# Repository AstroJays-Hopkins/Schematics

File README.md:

# Schematics

Permanent repository for schematics for all custom electrical hardware that is
created on this team. All custom electric devices, even non PCBs, should have 
a schematic here so we don't lose work.

## Development

Do note that KiCAD isn't fully merge compatible, so check with other people who
might be working on the schematic you modify before changing it. Changes to the
same file at the same time do no usually merge without manual intervention, so
one changeset will usually overwrite the other, causing loss of work.

### Prereqs

- KiCAD (install from [here](https://kicad-pcb.org/download/))
- FreeCAD (Optional, only needed if you need to make footprints or fix 3d models
  for mechanical)
- Understanding of good schematic drawing practices (see our resources section
  to learn more)

### Setup

1. Install KiCAD with 3D models if you have the disk space to spare. This will
   allow you to check you work with a board render
2. Open the `.pro` file with the same name as the project folder. All of the
   other `.pro` files are for the subsheets and should not be opened
   individually.

## Listing

- Actuator PCB - schematics for the circuits that control the higher voltage
  devices such as valves and solenoids
- Ignition-System - Provisional ignition control box ("football") schematics.
  Inaccurate due to missing wires in football and broken connections.
- Lib - Unified repository for all footprints, symbols and 3D models of the
  parts.
- Processor PCB - Schematics for the circuits that handle power distribution and
  inter-MCU communication.
- Prop-Avionics - Schematics for the (legacy) propulsion avionics system and
  DAQ plane
- Recovery PCB - Schematics for the circuits that control recovery ops such as
  altimeter and parachute deployment.
- Sensors PCB - Schematics for the circuits that handle analog to digital
  conversion and the filtering that goes with that.
- SolenoidRelay1 - Schematic for the solenoid control relay for connection to
  the raspberry pi.
- Transole - Prototype transistor based solenoid switching using GPIO level
  outputs and a heckin' large transistor (n-channel MOSFET). This is a *untested
  prototype* and should not be used in production until more research has been
  completed. Credit Sasha and Lin for research and design

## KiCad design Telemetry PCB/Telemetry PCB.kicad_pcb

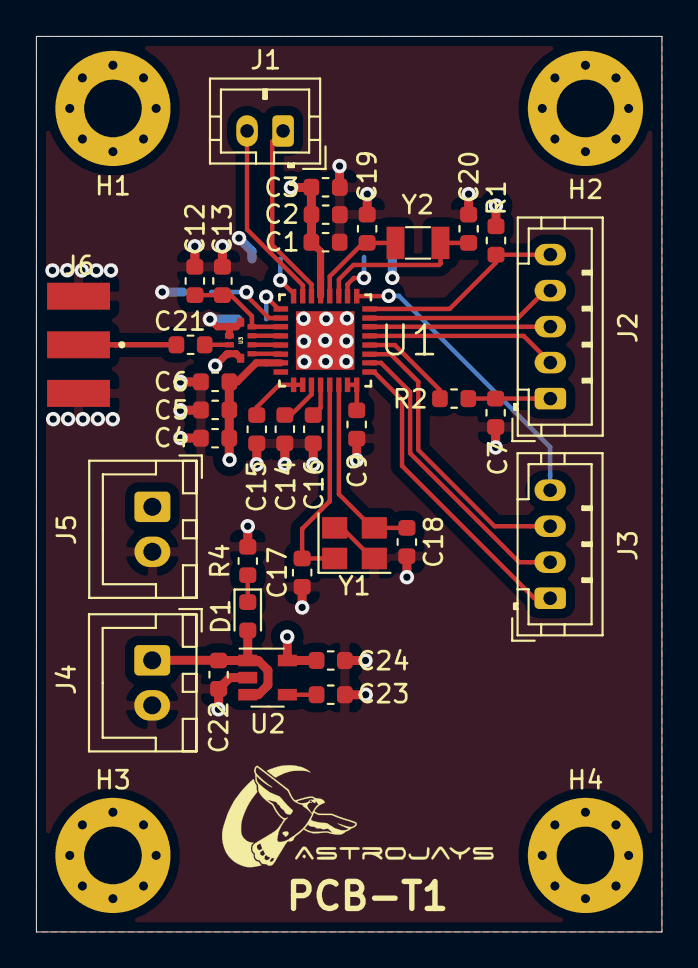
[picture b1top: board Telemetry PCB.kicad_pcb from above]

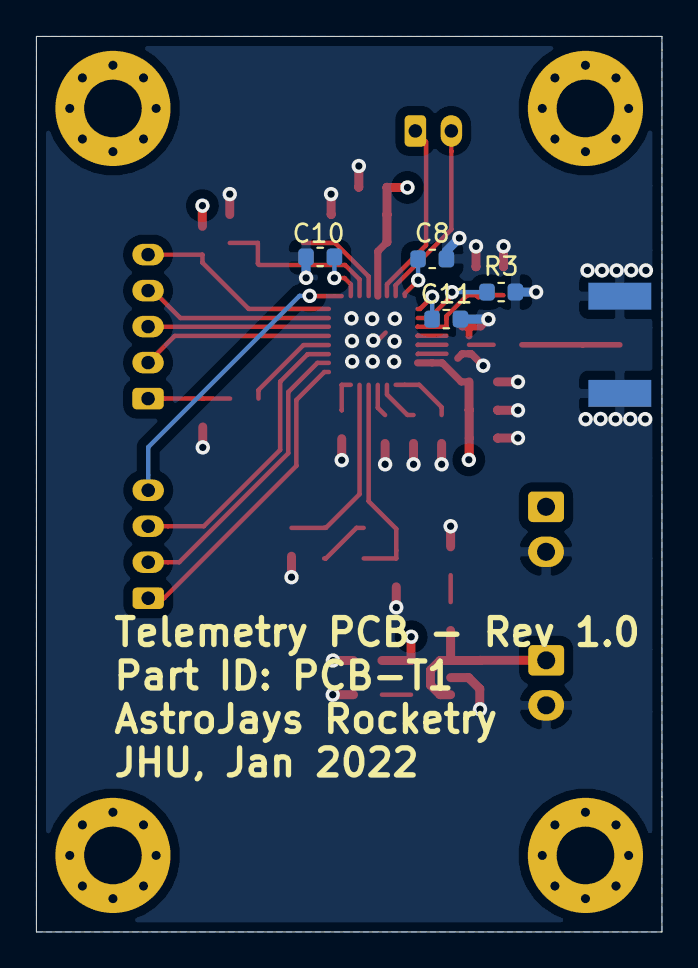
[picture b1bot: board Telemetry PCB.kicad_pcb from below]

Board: 4 copper layers, 34.8 x 49.8 mm, 44 parts (4 on the bottom side), 35 nets.

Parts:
C1, C4: 10u; C_0603_1608Metric
C2, C5, C8, C9, C10, C11, C12, C14, C15: 220n; C_0603_1608Metric
C3, C6: 100p; C_0603_1608Metric
C7: 1.5n; C_0603_1608Metric
C13, C17, C18: 18p; C_0603_1608Metric
C16: 150n; C_0603_1608Metric
C19, C20: 5.6p; C_0603_1608Metric
C21: 56p; C_0603_1608Metric
C22, C24: 2.2u; C_0603_1608Metric
C23: 10n; C_0603_1608Metric
D1: LED; LED_0603_1608Metric
H1, H2, H3, H4: MountingHole; MountingHole_3.2mm_M3_Pad_Via
J1: Conn_01x02_Male; JST_PH_B2B-PH-K_1x02_P2.00mm_Vertical
J2: Conn_01x05_Male; JST_PH_B5B-PH-K_1x05_P2.00mm_Vertical
J3: Conn_01x04_Male; JST_PH_B4B-PH-K_1x04_P2.00mm_Vertical
J4, J5: Conn_01x02_Male; JST_XH_B2B-XH-A_1x02_P2.50mm_Vertical
J6: CON-SMA-EDGE-S; RFSOLUTIONS_CON-SMA-EDGE-S
R1: 100k; R_0603_1608Metric
R2: 1.1k; R_0603_1608Metric
R3: 36k; R_0603_1608Metric
R4: 330; R_0603_1608Metric
U1: ADF7023-JBCPZ; QFN50P500X500X80-33N
U2: LP2985-3.3; SOT-23-5
U3: 0900PC15F0030
Y1: 26M; Crystal_SMD_3225-4Pin_3.2x2.5mm
Y2: 32.768k; Crystal_SMD_3215-2Pin_3.2x1.5mm

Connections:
+3V3: C1.1, C2.1, C3.1, C4.1, C5.1, C6.1, C24.1, J5.1, R1.2, U1.7, U1.29, U2.5
+5V: C22.1, D1.2, J4.1, U2.1, U2.3
/CREGRF2: C12.1, C13.1, U1.3, U3.9
/GP0: J3.1, U1.17
/GP1: J3.2, U1.18
/GP2: J3.3, U1.19
/GP4: J3.4, U1.25
/IRQ: R2.1, U1.20
/LNA_EN: J1.2, U1.31
/MISO: J2.2, U1.21
/MOSI: J2.4, U1.23
/OSC1: C20.1, U1.27, Y2.2
/OSC2: C19.1, U1.28, Y2.1
/PA_EN: J1.1, U1.30
/RFIO_1N: U1.5, U3.7
/RFIO_1P: U1.4, U3.8
/RFO2: U1.6, U3.6
/SCLK: J2.3, U1.22
/~CS: J2.5, R1.1, U1.24
GND: C1.2, C2.2, C3.2, C4.2, C5.2, C6.2, C7.1, C8.2, C9.2, C10.2, C11.2, C12.2, C13.2, C14.2, C15.2, C16.2, C17.2, C18.2, C19.2, C20.2, C22.2, C23.2, C24.2, J4.2, J5.2, J6.G1, J6.G2, J6.G3, J6.G4, R3.2, R4.2, U1.33, U2.2, U3.1, U3.2, U3.4, U3.5, U3.10, Y1.2, Y1.4
unnamed: C7.2, J2.1, R2.2
unnamed: C8.1, U1.32
unnamed: C9.1, U1.15, U1.16
unnamed: C10.1, U1.26
unnamed: C11.1, U1.1
unnamed: C14.1, U1.11
unnamed: C15.1, U1.9, U1.10
unnamed: C16.1, U1.12
unnamed: C17.1, U1.13, Y1.1
unnamed: C18.1, U1.14, Y1.3
unnamed: C21.1, U3.3
unnamed: C21.2, J6.1
unnamed: C23.1, U2.4
unnamed: D1.1, R4.1
unnamed: R3.1, U1.2

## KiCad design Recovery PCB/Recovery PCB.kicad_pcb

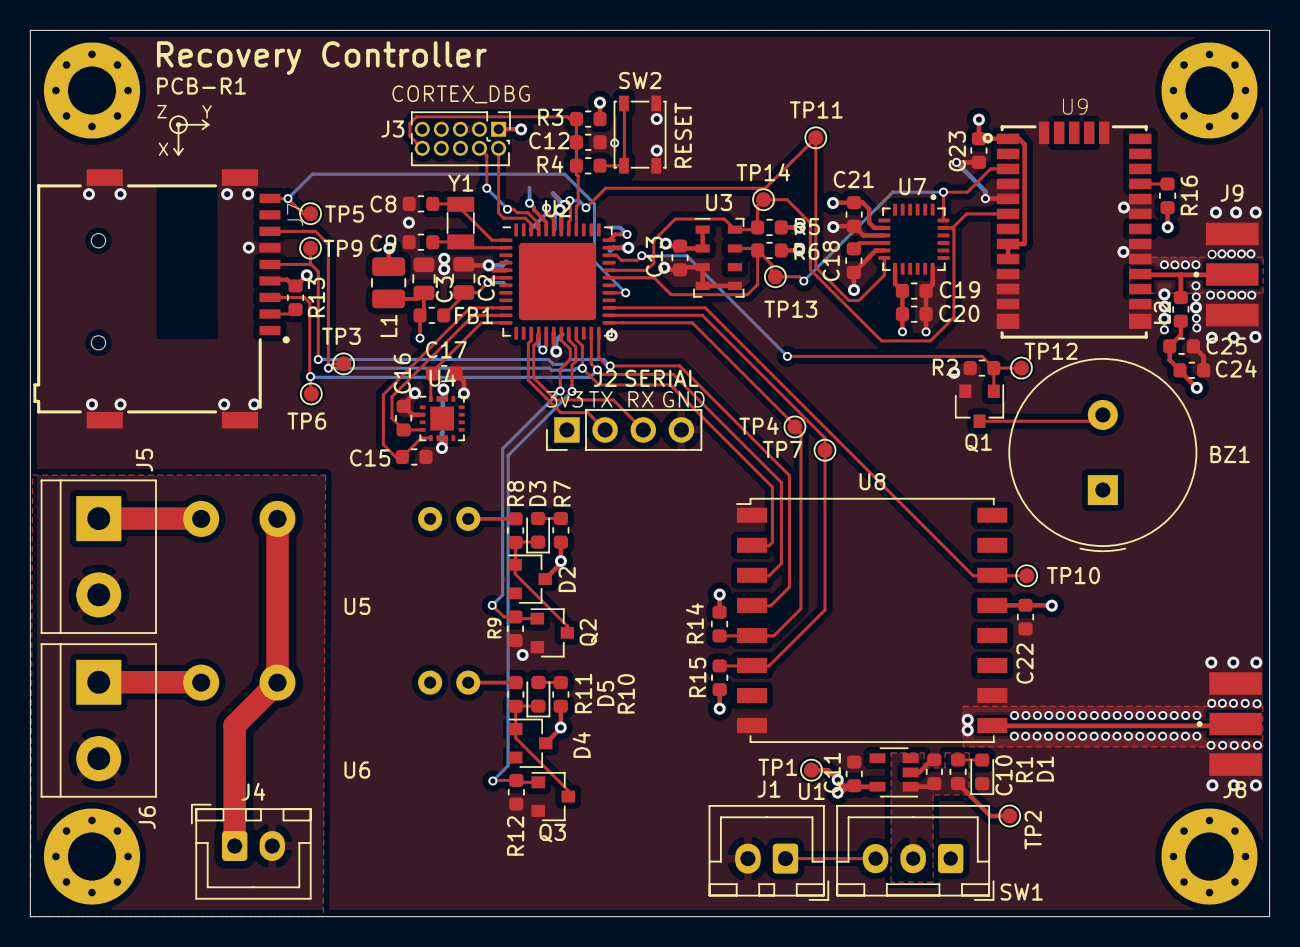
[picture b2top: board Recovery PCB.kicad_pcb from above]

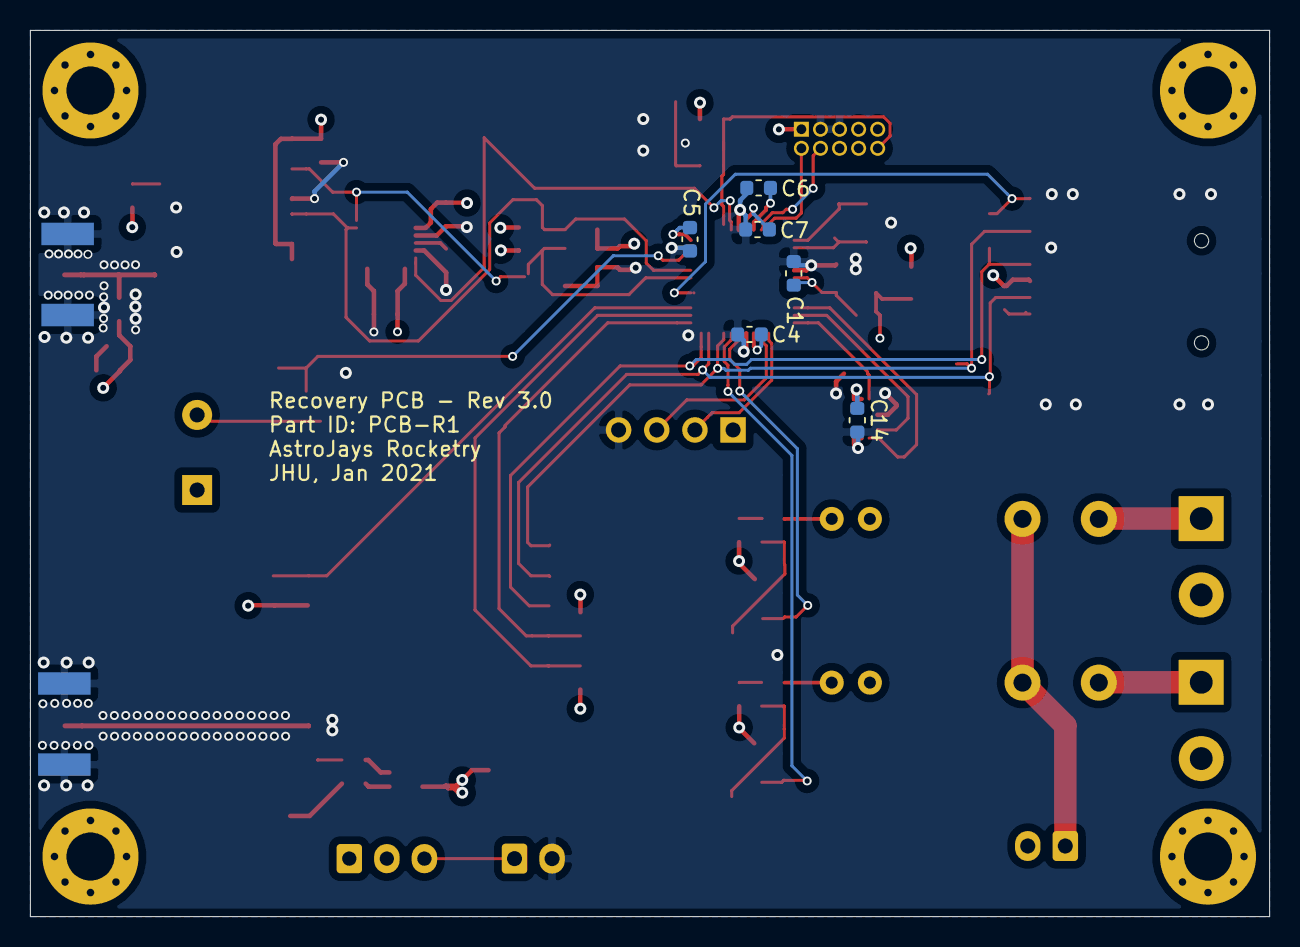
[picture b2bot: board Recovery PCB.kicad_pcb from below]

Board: 4 copper layers, 82.5 x 59.0 mm, 91 parts (6 on the bottom side), 48 nets.

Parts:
BZ1: Buzzer; Buzzer_TDK_PS1240P02BT_D12.2mm_H6.5mm
C1, C4, C5, C6, C12, C13, C14, C20, C22: 0.1u; C_0603_1608Metric
C2, C3: 10u; C_0805_2012Metric
C7: 1u; C_0603_1608Metric
C8, C9: 22p; C_0603_1608Metric
C10, C11: 10u; C_0603_1608Metric
C15, C16, C17: 0.01u; C_0603_1608Metric
C18: 0.47u; C_0603_1608Metric
C19: 2.2u; C_0603_1608Metric
C21: 10n; C_0603_1608Metric
C23: 4.7u; C_0603_1608Metric
C24: 47n; C_0603_1608Metric
C25: 1n; C_0603_1608Metric
D1, D3, D5: LED; LED_0603_1608Metric
D2, D4: D; D_SOT-23_ANK
FB1: Ferrite; L_0603_1608Metric
H1, H2, H3, H4: MountingHole; MountingHole_3.2mm_M3_Pad_Via
J1: Conn_01x02; JST_XH_B2B-XH-A_1x02_P2.50mm_Vertical
J2: Conn_01x04_Male; PinHeader_1x04_P2.54mm_Vertical
J3: MCU Programming Socket; PinHeader_2x05_P1.27mm_Vertical
J4: 9V_INPUT; JST_XH_B2B-XH-A_1x02_P2.50mm_Vertical
J5, J6: Screw_Terminal_01x02; TerminalBlock_bornier-2_P5.08mm
J7: MEM2075-00-140-01-A; GCT_MEM2075-00-140-01-A
J8: SMA_LORA; RFSOLUTIONS_CON-SMA-EDGE-S
J9: SMA_GPS; RFSOLUTIONS_CON-SMA-EDGE-S
L1: 10u; L_1008_2520Metric
L2: 47n; L_0603_1608Metric
Q1, Q2, Q3: BSS138; SOT-23
R1: 1k; R_0603_1608Metric
R2, R9, R12: 1M; R_0603_1608Metric
R3: 10k; R_0603_1608Metric
R4: 330; R_0603_1608Metric
R5, R6: 4.7k; R_0603_1608Metric
R7, R10: 220; R_0603_1608Metric
R8, R11: 10; R_0603_1608Metric
R13, R14, R15: 100k; R_0603_1608Metric
R16: 2.2k; R_0603_1608Metric
SW1: SW_SPDT; JST_XH_B3B-XH-A_1x03_P2.50mm_Vertical
SW2: SW_Push; SW_SPST_PTS815
TP1, TP2, TP12: TestPoint; TestPoint_Pad_D1.0mm
TP3: Espirus-misosu; TestPoint_Pad_D1.0mm
TP4: Radius-selectae; TestPoint_Pad_D1.0mm
TP5: Sandiscus-selectae; TestPoint_Pad_D1.0mm
TP6: Espirus-mosi; TestPoint_Pad_D1.0mm
TP7: Radius-reseta; TestPoint_Pad_D1.0mm
TP9: Espirus-chronos; TestPoint_Pad_D1.0mm
TP10: Radius-interruptus; TestPoint_Pad_D1.0mm
TP11: Emu-interruptus; TestPoint_Pad_D1.0mm
TP13: Etusi-sidae; TestPoint_Pad_D1.0mm
TP14: Etusi-chronos; TestPoint_Pad_D1.0mm
U1: XC6220B331MR; SOT-23-5
U2: ATSAMD21G17A-MUT; QFN-48-1EP_7x7mm_P0.5mm_EP5.15x5.15mm
U3: MS5607-02BA; LGA-8_3x5mm_P1.25mm
U4: ADXL377; LFCSP-16-3X3
U5, U6: Panasonic-PA-N
U7: ICM-20689; QFN50P400X400X95-24N
U8: RFM95W-915S2; HOPERF_RFM9XW_SMD
U9: CAM-M8
Y1: 32.768k; Crystal_SMD_3215-2Pin_3.2x1.5mm

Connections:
+3V3: BZ1.1, C11.1, C13.1, C14.1, C19.1, C20.1, C21.1, C22.1, C23.1, C24.1, C25.1, D2.1, D4.1, J2.1, J3.1, J7.P4, L1.1, L2.1, R3.1, R5.1, R6.1, R7.1, R10.1, R13.1, R14.1, R15.1, R16.1, TP1.1, U1.5, U3.1, U3.2, U4.14, U4.15, U5.2, U6.2, U7.8, U7.13, U8.13, U9.1, U9.8, U9.9
+9V: J4.1, U5.5, U6.5
+BATT: C10.1, R1.1, SW1.2, TP2.1, U1.1, U1.3
/BUZZER: Q1.1, R2.1, TP12.1, U2.34
/CLK: J7.P5, TP9.1, U2.24, U8.4
/IMU_INT: TP11.1, U2.41, U7.12
/IN1: Q2.1, R9.1, U2.19
/IN2: Q3.1, R12.1, U2.20
/MISO: J7.P7, TP3.1, U2.21, U8.2
/MOSI: J7.P3, TP6.1, U2.23, U8.3
/RADIO_CS: R14.2, TP4.1, U2.25, U8.5
/RADIO_IO: TP10.1, U2.27, U8.14
/RADIO_RESET: R15.2, TP7.1, U2.26, U8.6
/SCL: R5.2, TP14.1, U2.32, U3.8, U7.23, U9.6
/SDA: R6.2, TP13.1, U2.31, U3.7, U7.24, U9.3
/SD_CS: J7.P9, TP5.1, U2.29
/UART_RX: J2.3, U2.16
/UART_TX: J2.2, U2.15
/Xout: C15.1, U2.10, U4.5
/Yout: C16.1, U2.11, U4.4
/Zout: C17.1, U2.12, U4.16
/gps-module/GPS_RF: J9.1, L2.2, U9.17
/gps-module/~RST: R16.2, U9.23
/radio-915-lora/LoRa_RF: J8.1, U8.9
GND: C1.2, C2.2, C3.2, C4.2, C5.1, C6.1, C7.2, C8.1, C9.1, C10.2, C11.2, C12.2, C13.2, C14.2, C15.2, C16.2, C17.2, C18.2, C19.2, C20.2, C21.2, C22.2, C23.2, C24.2, C25.2, D1.1, J1.2, J2.4, J3.3, J3.5, J7.P6, J7.SH1, J7.SH2, J7.SH3, J7.SH4, J8.G1, J8.G2, J8.G3, J8.G4, J9.G1, J9.G2, J9.G3, J9.G4, Q1.2, Q2.2, Q3.2, R2.2, R9.2, R12.2, SW2.1, U1.2, U2.5, U2.18, U2.35, U2.42, U3.3, U3.4, U3.5, U4.2, U4.6, U4.7, U7.9, U7.11, U7.18, U8.1, U8.8, U8.10, U9.4, U9.5, U9.10, U9.11, U9.12, U9.13, U9.14, U9.15, U9.18, U9.19, U9.21, U9.22, U9.27, U9.31
GNDPWR: J4.2, J5.2, J6.2
unnamed: BZ1.2, Q1.3
unnamed: C1.1, C2.1, FB1.1, U2.6
unnamed: C3.1, C4.1, C5.2, C6.2, FB1.2, L1.2, U2.17, U2.36, U2.44
unnamed: C7.1, U2.43
unnamed: C8.2, U2.1, Y1.1
unnamed: C9.2, U2.2, Y1.2
unnamed: C12.1, J3.10, R3.2, R4.1, U2.40
unnamed: C18.1, U7.10
unnamed: D1.2, R1.2
unnamed: D2.2, D3.1, Q2.3, R8.2
unnamed: D3.2, R7.2
unnamed: D4.2, D5.1, Q3.3, R11.2
unnamed: D5.2, R10.2
unnamed: J1.1, SW1.3
unnamed: J3.2, U2.46
unnamed: J3.4, U2.45
unnamed: J5.1, U5.6
unnamed: J6.1, U6.6
unnamed: J7.P2, R13.2
unnamed: R4.2, SW2.2
unnamed: R8.1, U5.1
unnamed: R11.1, U6.1

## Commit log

2019-09-24 Schamtics: Add initial thermocouple drawings
    Very WIP and footprints need cleaning.
2019-09-28 schemtics/thermocouples: Clean file structure
    Cleaned up backups and whatnot to make things nicer.
2019-09-28 Prop-Avionics: Modularize Schematic
    Break up components into sub schematics to make collaboration easier.
2019-09-28 Prop-Avionics: Add boilerplate
    Boilerplated solenoids and pressure transducers.
2019-09-29 schematics: Add Prototype for Transistor Solenoid
    Added a schematic for the prototype transistor solenoid switching system
    to preserve documentation of work conducted today. This is an
    alternative to the (undocumented) relay switching system that was used
    previously.
2019-09-29 schematics/README.md: Update List
    Added Transole and Prop-Avionics To the listing of schematic projects
    contained within this repo.
2019-09-29 Schema: added PT to PCB library
    Update to PCB library with new part used for PTs
2019-10-04 Flipped flyback diode.
2019-10-04 Modify symbol library table to remove system-specific library paths
2019-10-04 Schema: Add Solenoid Relay
    Both solenoids (normally open and normally closed) use this schematic.
    (Position of the pin changes for normally open/closed)
2019-10-04 Schema: added football
    Preliminary documentation of football ignition system,
    need fixes to panel wiring.
2019-10-04 Schema: Flip flyback in relay
    Solenoidrelay schematic had backwards flyback diode.
2019-10-04 Schema: Update README
    Included `SolenoidRelay1` and `Ignition-System` in schematics listing.
2019-10-16 schema: Update Ignition-System
    Updated schematic to match current control surfaces and plans for
    extensions to the ground interface.
2019-10-26 specs/Prop-Avionics: Update with I2C protocol defs
    Added basic I2c protocol specs to standardize implementation across all
    devices that will communicate on this bus. Design is still pending and
    may not work as speced.
2020-02-12 Create new schematics for Analog Flight PCBs.
    These schematics include the circuits for the thermocouples as well as the
    pressure transducers. Unlike previous iterations, they include resistors
    and capacitors necessary for the PCB.
2020-02-14 Updated schematics for Analog Flight PCB and drew preliminary schematics for Recovery PCB.
2020-02-14 Finished layout for individual components and prepping for I2C and power connections.
2020-02-14 schematics: Create Graphics lib
    Created new library for team-specific logos and graphics for PCBs.
2020-02-14 ASPCB: Board cleanup
    Fixed loadcell connection and cleaned up references. Also replaced silk
    screen with edge cuts.
2020-02-14 ASPCB: Revision 1.0c
    Changed all single row plug connectors to JST-PH instead of JST-XH to
    save space. All routes were optimized to place passives closer to ICs
    and contacts. Two additional LC reader assemblies were added for test
    config. Testpoints have been added on both 3v3 and 5v power supplies for
    testing. Power and ground have been moved into primary connector, with
    interleaving to preserve signal integrity. First attempt at a ground
2020-02-14 ASPCB: Rev 1.0d
    Added three new TC ADCs per prop request. Loadcell interfaces had
    conflicting I2C addresses so a TI PCA9548 8ch I2C switch was added.
    PT supply voltage was changed from 3V3 to 5V. I2C level shifter using
    MOSFETs per Phillips AN97055 was added to ensure I2C bus reliability.
    Extra 5V power supply pin removed since one pin supplies up to 1A, far
    above the max current draw of this board. Traces have been rerouted for
2020-02-14 Changed screw terminals to JST connectors and added two more connectors to the PTs.
2020-02-14 Finish connecting analog flight PCB components and start PCB layout.
2020-02-14 ASPCB: Move Loadcell.lib to Components.lib
    Moved loacell library to general components library and added fixed
    MAX31856 part with correct tristate SDO.
2020-02-14 ASPCB: Reroute and add datasheets
    Rerouted copper trace to intersect with other trace at via instead of
    three-point intersection; added datasheets for NAU7802SGI ADC chip and
    others.
2020-02-14 Separated all components to make traces easier.
2020-02-14 schema: Complete prelim. AFPCB design
    Preliminary PCB design for Analog Flight Board completed. Needs further
    review.
2020-02-14 ASPCB: Rev 1.0g
    Final revision in the 1.0 series, adding power-on indicator and low pass
    filtering for ADC @ 1.59kHz to prevent aliasing. This revision is ready
    for fab and prototyping. Obsolete PCA9548A has been replaced by current
    part TCA9548A.
2020-02-14 schema: Restructure Lib
    Moved all footprints into new directory to prepare for new parts
2020-02-14 ASPCB: Rev 1.0e
    Optimized routing to prevent tombstoning. Analog trace lengths were
    further shortened, and extranious traces were removed. uCs have been
    renumbered to be fully consecutive.
2020-02-14 ASPCB: Rev 1.0f
    Rerouted with DRDY select lines to I2C GPIO expander. This means that we
    can check all of the DRDY lines with one interrupt, so long as we poll
    the input expander after recieving each interrupt. This allows us to
    switch to interrupt driven programming, which should enhance the data
    collection speed while reducing CPU use. To accomodate the extra lines,
    we have switched to gridded ground style routing.
2020-02-14 schema/Lib: Add new parts
    Added 3d model for the JST connector and the new symbols and footprint
    for the ATSAMD21G
2020-02-14 Update actuator board schematic.
2020-02-14 Added SAMD21G uC and crystal, RFM95 radio and supporting circuitry.
2020-02-14 Added power uC RCL filter network and reset circuitry and preliminary circuitry for GPS module.
2020-02-14 Removed SD card level shifter, added pins and connections to GPS.
2020-02-14 .gitignore: Initialize with sane defaults
    Copied from old `Misc` repo.
2020-02-14 .gitattributes: Normalize files to UNIX line ends
    Windows line ends are not standards compliant and break everything.
    Forcing git to only commit unix ones is much saner and prevents
    mysterious breakages.
2020-02-14 Rec PCB: Fix libs
    Moved libs to correct lib folder and changed footprint format to new
    kicad format.
2020-02-21 Update schematic for actuator board. Needs further review.
2020-02-22 Analog Flight PCB: Move directories
    Moved analog flight PCB to Sensors PCB to reflect actual function as a
    general purpose sensors interface, not just for flight.
2020-02-22 README: Update with instructions
    Updated READ.md with contribution instructions and a more accurate
    listing of the projects contained within this repo.
2020-02-22 Lib: Edit ATSAMD21G pins
    Merged all digital ground pins into one pin to declutter schematics
    drawn with this part.
2020-02-22 Proc PCB: Add Initial schematic
    Added all MCUs and headers to schematic to get primary layout.
2020-02-28 Update relays on actuators.
2020-03-07 Update actuator board with new optoisolators. Also added more connections.
2020-03-07 Lib: Add TLP291 part
    Added TLP291-4 4 channel optoisolator parts and footprints to project
    library. Note that this is a multi-unit symbol that needs to have its
    power unit placed to function.
2020-03-07 Updated recovery board with new connections.
2020-03-07 Update relays and re-annotate entire schematic. Review needed before layout.
2020-03-07 Update relays on recovery board.
2020-03-08 Added footprints.
    Added footprints for various parts. Still need to update some more and calculate some values.
2020-07-01 Drew up power supply, test points; reworked MCU I/O
2020-07-04 Processor PCB: Add commproc
    Added schematics for communications processor, and started engine
    processor.
2020-07-04 lib: Add IFX007TAUMA1
    Added the Infineon half-bridge driver to be used for motor control.
2020-07-04 Actuator PCB: Redraw with new symbol
    Redrew schematic to follow subsystem guidelines and updated symbole to
    our new vendored symbol that adheres to subsystem schematic symbol
    guidelines.
2020-09-21 Actuators PCB: Add footprints
    Finished off schematic; board is ready for layout now.
2020-10-18 Added custom libraries local to project.
2020-11-14 Updated some footprints and re-annotated schematic.
2020-12-06 Added missing footprints and replaced GPS module.
2020-12-29 Finished Revision 1 of the Recovery PCB.
2021-01-11 Finished Rev 2 of the Recovery PCB. Optimized trace lengths and relays.
2021-01-11 Recovery PCB: Redraw schematics
    Redrew Recover PCB schematics to be more easily readable and fixed board
    outline, adding netclasses to ease trace placement.
2021-01-12 Rev 3 of Recovery PCB. Fixed decoupling caps and finalized power/ground.
2021-01-12 Recovery PCB: Optimize space
    Reduced board space by shifting layout a bit.
2021-01-12 Recovery PCB: Reannotate
    Reannotated schematic to fix reference numbering and keep reference
    designators consistent.
2021-01-12 Recovery PCB: Tweak Motion Axes
    Reconciled IMU and accelerometer motion axes and added models for edge
    connectors.
2021-01-13 Recovery PCB: Fix relay
    Replaced unavailable relay with a correct part and replaced voltage
    regulator with an easier to solder alternative.
2021-01-23 Recovery PCB: Add coplanar wave guide for GPS RF trace.
2021-01-23 Recovery PCB: Deleted excess pullup resistors, redid mounting holes.
2021-01-27 Recovery PCB: Minor changes to layout.
2021-02-14 Recovery: Finalize PCB.
2021-03-13 Recovery PCB: Add active antenna supply circuit.
2021-10-02 Replaced IMU, relays, and power regulator with new components. Modified schematic accordingly.
2021-10-04 Reperformed board layout with new components.
2021-11-07 Telemetry PCB: Initial schematic capture finished.
2021-12-23 Telemetry PCB: Add libraries for transceiver module.
2021-12-23 Telemetry PCB: Add recommended values for passives.
2021-12-29 Telemetry PCB: Added impedance matched filter symbol.
2022-01-03 Telemetry PCB: Updated schematic to match application note.
2022-01-05 Telemetry PCB: Updated footprints and finalized schematic.
2022-01-06 Telemetry PCB: Finished first iteration of board layout.
2022-01-10 Telemetry PCB: Fixed various clearance issues and improved layout.
2022-02-18 Telemetry PCB: Minor fixes
2022-02-20 Generated Gerber and drill files for telemetry and recovery boards
